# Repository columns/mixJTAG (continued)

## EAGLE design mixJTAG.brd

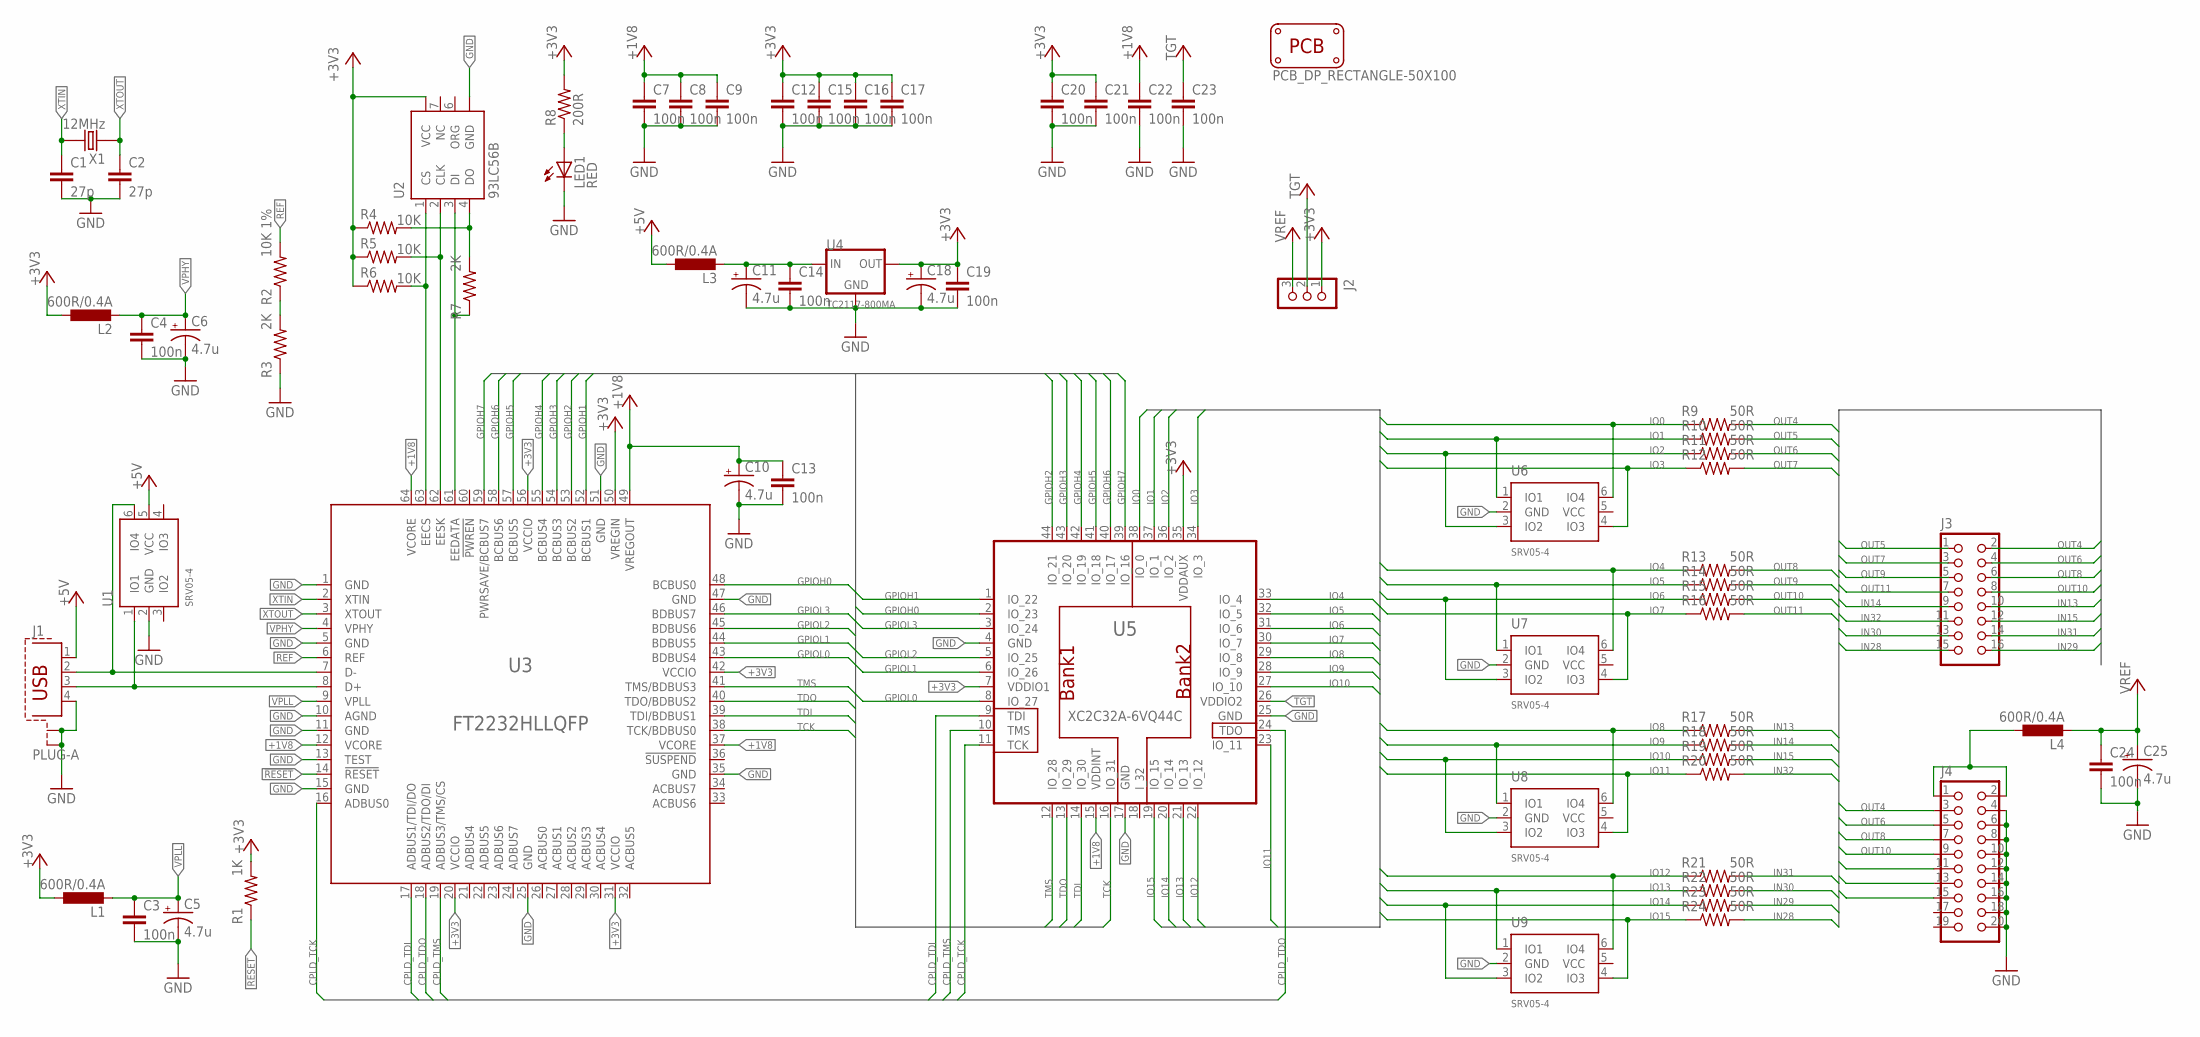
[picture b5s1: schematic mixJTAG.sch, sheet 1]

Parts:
C1, C2: 27p; C0805
C3, C4, C7, C8, C9, C12, C13, C14, C15, C16, C17, C19, C20, C21, C22, C23, C24: 100n; C0805
C5, C6, C10, C11, C18, C25: 4.7u; A/3216-18R
J1: PLUG-A; USB-A-HOLE-PLUG
J2: CON_HEADER_1X03-PTH; M1X3
J3: CON_HEADER_2X08; M2X8
J4: CON_HEADER_2X10-PTH; M2X10
L1, L2, L3, L4: 600R/0.4A; L2012C
LED1: RED; CHIP-LED0805
PCB1: PCB_DP_RECTANGLE-50X100; DP10050_V1
R1: 1K; R0805
R2: 10K 1%; R0805
R3, R7: 2K; R0805
R4, R5, R6: 10K; R0805
R8: 200R; R0805
R9, R10, R11, R12, R13, R14, R15, R16, R17, R18, R19, R20, R21, R22, R23, R24: 50R; R0805
U1, U6, U7, U8, U9: SRV05-4; SOT23-6
U2: 93LC56B; SOIC8
U3: FT2232HLLQFP; LQFP-64
U4: TC2117-800MA; SOT223
U5: XC2C32A-6VQ44C; VQ-44
X1: 12MHz; IQG5032A

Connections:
!RESET: R1.1, U3.14 (!RESET)
+1V8: C7.1, C8.1, C9.1, C10.+, C13.1, C22.1, U3.12 (VCORE), U3.37 (VCORE), U3.49 (VREGOUT), U3.64 (VCORE), U5.15 (VDDINT)
+3V3: C12.1, C15.1, C16.1, C17.1, C18.+, C19.1, C20.1, C21.1, J2.1, L1.1, L2.1, R1.2, R4.1, R5.1, R6.1, R8.2, U2.8 (VCC), U3.20 (VCCIO), U3.31 (VCCIO), U3.42 (VCCIO), U3.50 (VREGIN), U3.56 (VCCIO), U4.2 (OUT), U5.7 (VDDIO1), U5.35 (VDDAUX)
+5V: J1.1, L3.1, U1.5 (VCC)
CPLD_TCK: U3.16 (ADBUS0), U5.11 (TCK)
CPLD_TDI: U3.17 (ADBUS1/TDI/DO), U5.9 (TDI)
CPLD_TDO: U3.18 (ADBUS2/TDO/DI), U5.24 (TDO)
CPLD_TMS: U3.19 (ADBUS3/TMS/CS), U5.10 (TMS)
EECS: R6.2, U2.1 (CS), U3.63 (EECS)
EEDATA: R7.1, U2.3 (DI), U3.61 (EEDATA)
EESK: R5.2, U2.2 (CLK), U3.62 (EESK)
GND: C1.2, C2.2, C3.2, C4.2, C5.-, C6.-, C7.2, C8.2, C9.2, C10.-, C11.-, C12.2, C13.2, C14.2, C15.2, C16.2, C17.2, C18.-, C19.2, C20.2, C21.2, C22.2, C23.2, C24.2, C25.-, J1.4, J1.S1, J1.S2, J4.4, J4.6, J4.8, J4.10, J4.12, J4.14, J4.16, J4.18, J4.20, LED1.C, R3.1, U1.2 (GND), U2.5 (GND), U3.1 (GND), U3.5 (GND), U3.10 (AGND), U3.11 (GND), U3.13 (TEST), U3.15 (GND), U3.25 (GND), U3.35 (GND), U3.47 (GND), U3.51 (GND), U4.1 (GND), U5.4 (GND), U5.17 (GND), U5.25 (GND), U6.2 (GND), U7.2 (GND), U8.2 (GND), U9.2 (GND)
GPIOH0: U3.48 (BCBUS0), U5.2 (IO_23)
GPIOH1: U3.52 (BCBUS1), U5.1 (IO_22)
GPIOH2: U3.53 (BCBUS2), U5.44 (IO_21)
GPIOH3: U3.54 (BCBUS3), U5.43 (IO_20)
GPIOH4: U3.55 (BCBUS4), U5.42 (IO_19)
GPIOH5: U3.57 (BCBUS5), U5.41 (IO_18)
GPIOH6: U3.58 (BCBUS6), U5.40 (IO_17)
GPIOH7: U3.59 (PWRSAVE/BCBUS7), U5.39 (IO_16)
GPIOL0: U3.43 (BDBUS4), U5.8 (IO_27)
GPIOL1: U3.44 (BDBUS5), U5.6 (IO_26)
GPIOL2: U3.45 (BDBUS6), U5.5 (IO_25)
GPIOL3: U3.46 (BDBUS7), U5.3 (IO_24)
IN13: J3.10, J4.11, R17.2
IN14: J3.9, R18.2
IN15: J3.12, J4.13, R19.2
IN28: J3.15, R24.2
IN29: J3.16, R23.2
IN30: J3.13, R22.2
IN31: J3.14, J4.15, R21.2
IN32: J3.11, R20.2
IO0: R9.1, U5.38 (IO_0), U6.6 (IO4)
IO1: R10.1, U5.37 (IO_1), U6.1 (IO1)
IO2: R11.1, U5.36 (IO_2), U6.3 (IO2)
IO3: R12.1, U5.34 (IO_3), U6.4 (IO3)
IO4: R13.1, U5.33 (IO_4), U7.6 (IO4)
IO5: R14.1, U5.32 (IO_5), U7.1 (IO1)
IO6: R15.1, U5.31 (IO_6), U7.3 (IO2)
IO7: R16.1, U5.30 (IO_7), U7.4 (IO3)
IO8: R17.1, U5.29 (IO_8), U8.6 (IO4)
IO9: R18.1, U5.28 (IO_9), U8.1 (IO1)
IO10: R19.1, U5.27 (IO_10), U8.3 (IO2)
IO11: R20.1, U5.23 (IO_11), U8.4 (IO3)
IO12: R21.1, U5.22 (IO_12), U9.6 (IO4)
IO13: R22.1, U5.21 (IO_13), U9.1 (IO1)
IO14: R23.1, U5.20 (IO_14), U9.3 (IO2)
IO15: R24.1, U5.19 (IO_15), U9.4 (IO3)
unnamed: J1.2, U1.6 (IO4), U3.7 (D-)
unnamed: J1.3, U1.1 (IO1), U3.8 (D+)
unnamed: C11.+, C14.1, L3.2, U4.3 (IN)
unnamed: J4.1, J4.2, L4.1
unnamed: R2.1, R3.2
unnamed: LED1.A, R8.1
unnamed: R4.2, R7.2, U2.4 (DO)
OUT4: J3.2, J4.3, R9.2
OUT5: J3.1, R10.2
OUT6: J3.4, J4.5, R11.2
OUT7: J3.3, R12.2
OUT8: J3.6, J4.7, R13.2
OUT9: J3.5, R14.2
OUT10: J3.8, J4.9, R15.2
OUT11: J3.7, R16.2
REF: R2.2, U3.6 (REF)
TCK: U3.38 (TCK/BDBUS0), U5.16 (IO_31)
TDI: U3.39 (TDI/BDBUS1), U5.14 (IO_30)
TDO: U3.40 (TDO/BDBUS2), U5.13 (IO_29)
TGT: C23.1, J2.2, U5.26 (VDDIO2)
TMS: U3.41 (TMS/BDBUS3), U5.12 (IO_28)
VPHY: C4.1, C6.+, L2.2, U3.4 (VPHY)
VPLL: C3.1, C5.+, L1.2, U3.9 (VPLL)
VREF: C24.1, C25.+, J2.3, L4.2
XTIN: C1.1, U3.2 (XTIN), X1.P$2 (2)
XTOUT: C2.1, U3.3 (XTOUT), X1.P$1 (1)

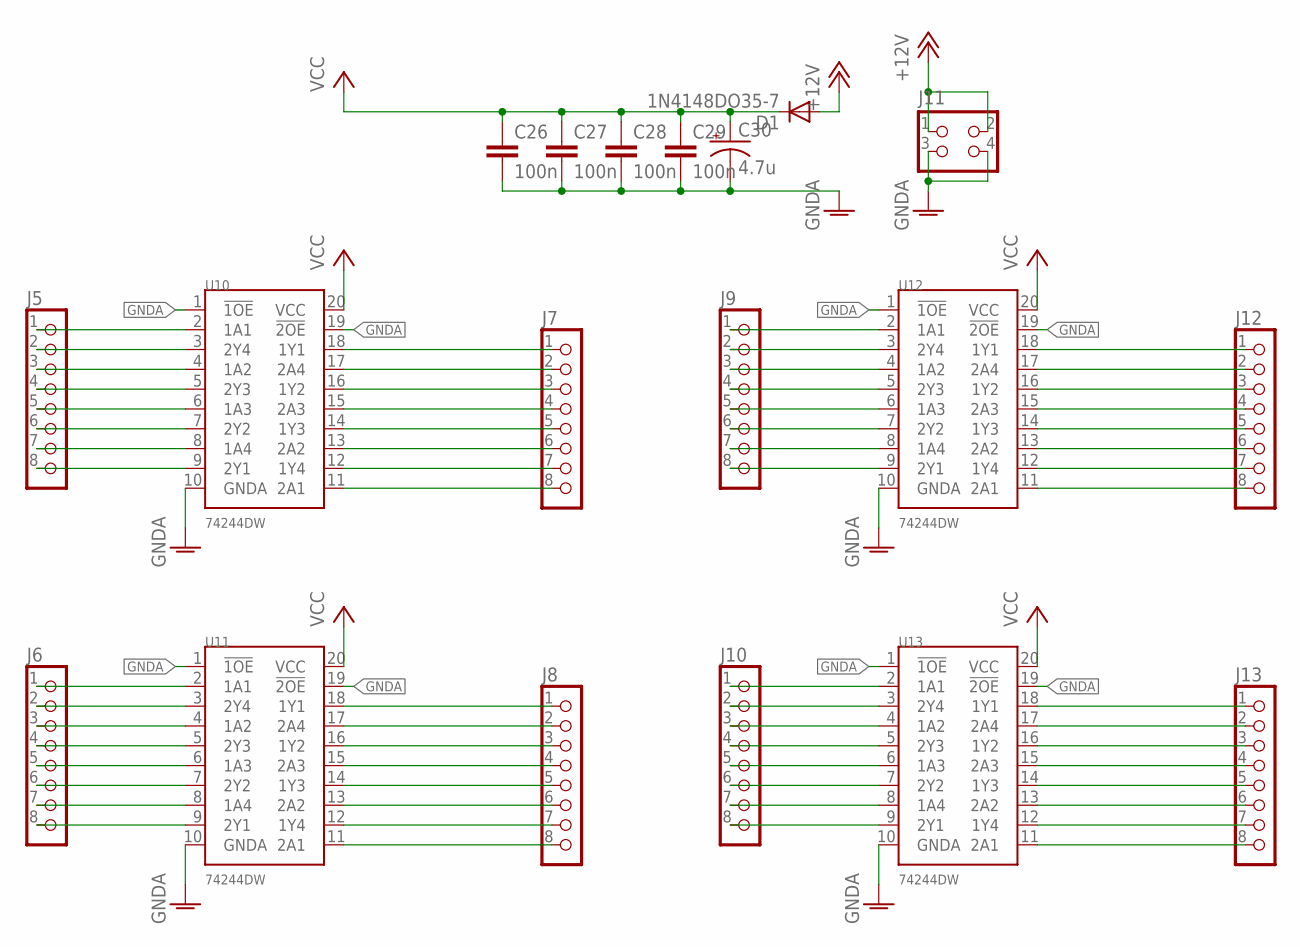
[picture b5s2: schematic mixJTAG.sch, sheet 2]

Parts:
C26, C27, C28, C29: 100n; C0805
C30: 4.7u; A/3216-18R
D1: 1N4148DO35-7; DO35-7
J5, J6, J7, J8, J9, J10, J12, J13: CON_HEADER_1X08-PTH; M1X8
J11: CON_HEADER_2X02-PTH; M2X2
U10, U11, U12, U13: 74244DW; SO20W

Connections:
+12V: D1.A, J11.1, J11.2
GNDA: C26.2, C27.2, C28.2, C29.2, C30.-, J11.3, J11.4, U10.1 (!1OE), U10.10 (GNDA), U10.19 (!2OE), U11.1 (!1OE), U11.10 (GNDA), U11.19 (!2OE), U12.1 (!1OE), U12.10 (GNDA), U12.19 (!2OE), U13.1 (!1OE), U13.10 (GNDA), U13.19 (!2OE)
unnamed: J5.8, U10.9 (2Y1)
unnamed: J5.7, U10.8 (1A4)
unnamed: J5.6, U10.7 (2Y2)
unnamed: J5.5, U10.6 (1A3)
unnamed: J5.4, U10.5 (2Y3)
unnamed: J5.3, U10.4 (1A2)
unnamed: J5.2, U10.3 (2Y4)
unnamed: J5.1, U10.2 (1A1)
unnamed: J7.8, U10.11 (2A1)
unnamed: J7.7, U10.12 (1Y4)
unnamed: J7.6, U10.13 (2A2)
unnamed: J7.5, U10.14 (1Y3)
unnamed: J7.4, U10.15 (2A3)
unnamed: J7.3, U10.16 (1Y2)
unnamed: J7.2, U10.17 (2A4)
unnamed: J7.1, U10.18 (1Y1)
unnamed: J6.8, U11.9 (2Y1)
unnamed: J6.7, U11.8 (1A4)
unnamed: J6.6, U11.7 (2Y2)
unnamed: J6.5, U11.6 (1A3)
unnamed: J6.4, U11.5 (2Y3)
unnamed: J6.3, U11.4 (1A2)
unnamed: J6.2, U11.3 (2Y4)
unnamed: J6.1, U11.2 (1A1)
unnamed: J8.8, U11.11 (2A1)
unnamed: J8.7, U11.12 (1Y4)
unnamed: J8.6, U11.13 (2A2)
unnamed: J8.5, U11.14 (1Y3)
unnamed: J8.4, U11.15 (2A3)
unnamed: J8.3, U11.16 (1Y2)
unnamed: J8.2, U11.17 (2A4)
unnamed: J8.1, U11.18 (1Y1)
unnamed: J9.8, U12.9 (2Y1)
unnamed: J9.7, U12.8 (1A4)
unnamed: J9.6, U12.7 (2Y2)
unnamed: J9.5, U12.6 (1A3)
unnamed: J9.4, U12.5 (2Y3)
unnamed: J9.3, U12.4 (1A2)
unnamed: J9.2, U12.3 (2Y4)
unnamed: J9.1, U12.2 (1A1)
unnamed: J12.8, U12.11 (2A1)
unnamed: J12.7, U12.12 (1Y4)
unnamed: J12.6, U12.13 (2A2)
unnamed: J12.5, U12.14 (1Y3)
unnamed: J12.4, U12.15 (2A3)
unnamed: J12.3, U12.16 (1Y2)
unnamed: J12.2, U12.17 (2A4)
unnamed: J12.1, U12.18 (1Y1)
unnamed: J10.8, U13.9 (2Y1)
unnamed: J10.7, U13.8 (1A4)
unnamed: J10.6, U13.7 (2Y2)
unnamed: J10.5, U13.6 (1A3)
unnamed: J10.4, U13.5 (2Y3)
unnamed: J10.3, U13.4 (1A2)
unnamed: J10.2, U13.3 (2Y4)
unnamed: J10.1, U13.2 (1A1)
unnamed: J13.8, U13.11 (2A1)
unnamed: J13.7, U13.12 (1Y4)
unnamed: J13.6, U13.13 (2A2)
unnamed: J13.5, U13.14 (1Y3)
unnamed: J13.4, U13.15 (2A3)
unnamed: J13.3, U13.16 (1Y2)
unnamed: J13.2, U13.17 (2A4)
unnamed: J13.1, U13.18 (1Y1)
VCC: C26.1, C27.1, C28.1, C29.1, C30.+, D1.C, U10.20 (VCC), U11.20 (VCC), U12.20 (VCC), U13.20 (VCC)

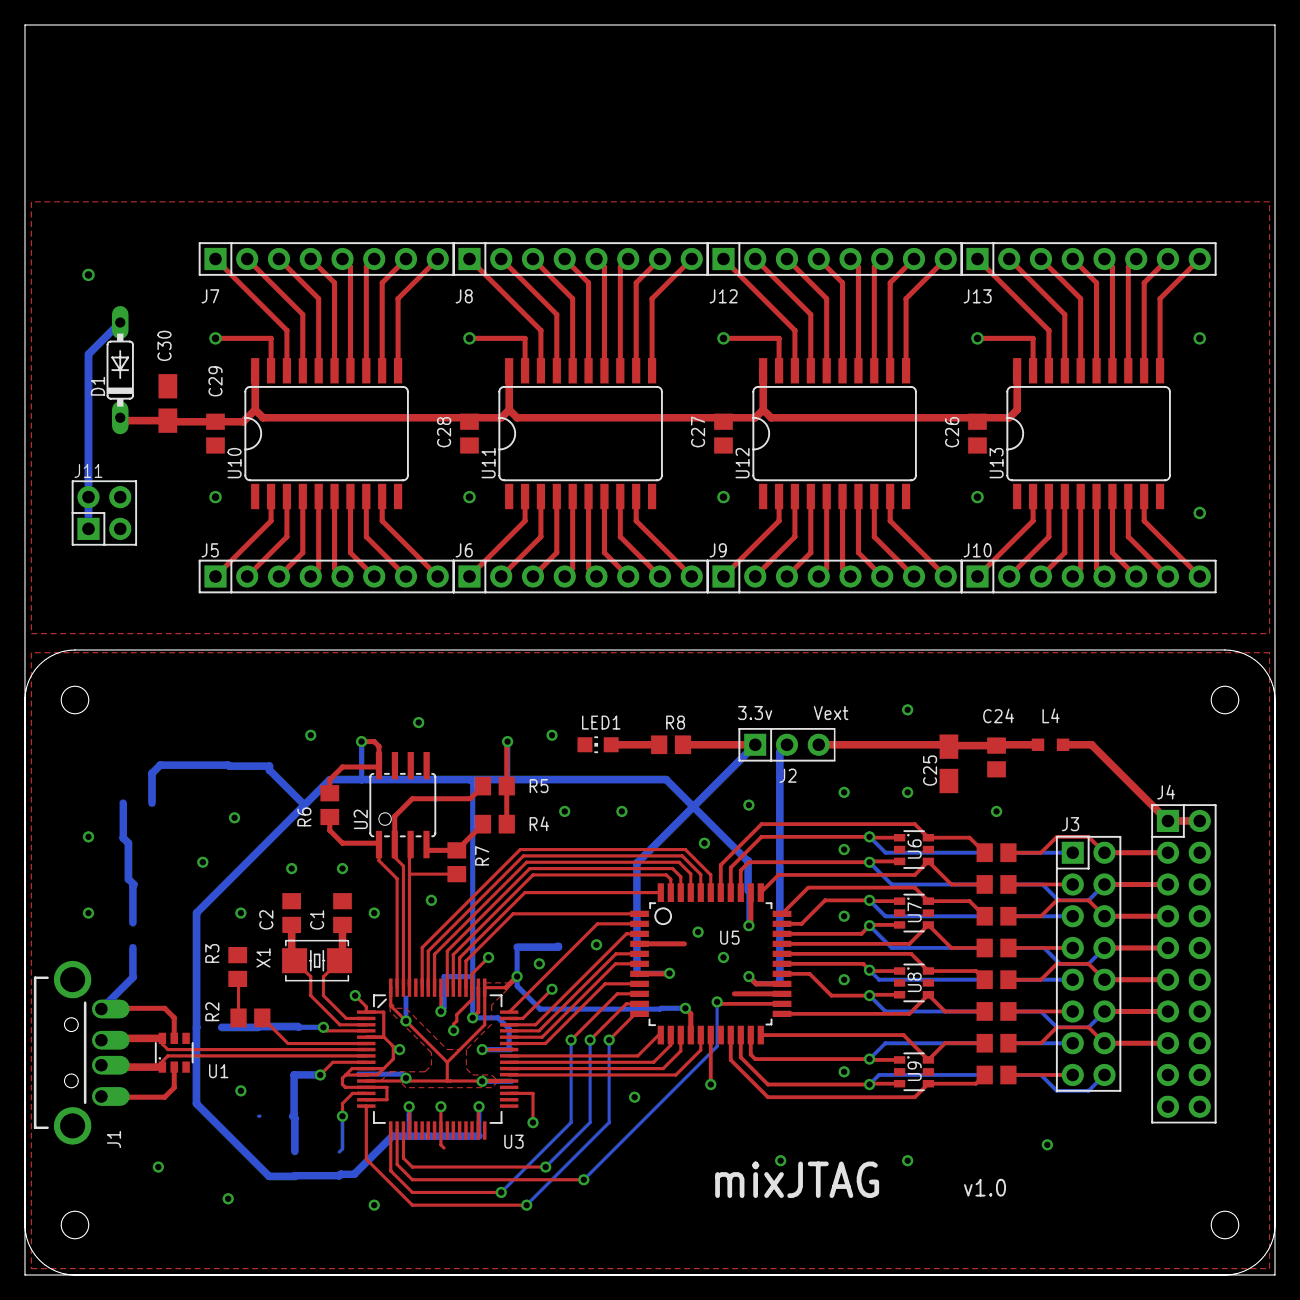
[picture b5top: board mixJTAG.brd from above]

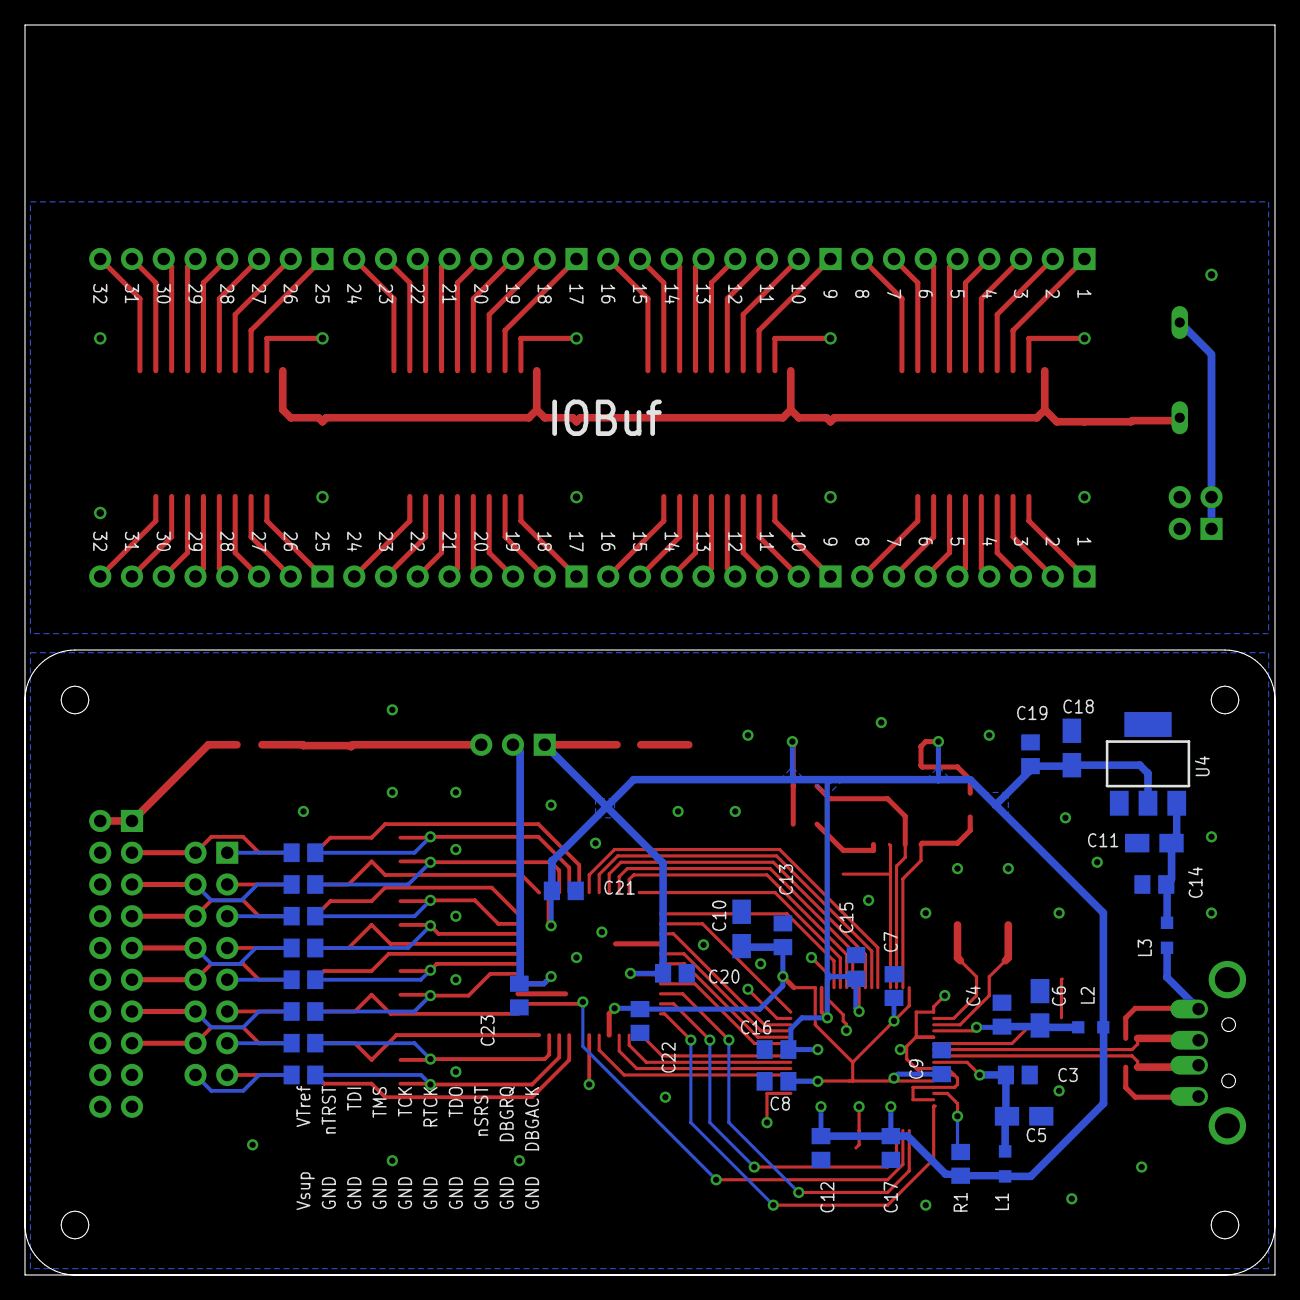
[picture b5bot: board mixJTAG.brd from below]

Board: 2 copper layers, 100.0 x 100.0 mm, 88 parts (34 on the bottom side), 141 nets.

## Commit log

2015-01-22 initial version
2015-01-22 first layout
2015-01-22 change usb pad
2015-01-22 back up committing
2015-01-22 mov ldo to bottom
2015-01-22 more via
2015-01-22 add io buffer board
2015-01-22 change to 0805 current limit resistor
2015-01-22 add libs, cam job script,design rule check
2015-01-22 more output
2015-01-24 backup
